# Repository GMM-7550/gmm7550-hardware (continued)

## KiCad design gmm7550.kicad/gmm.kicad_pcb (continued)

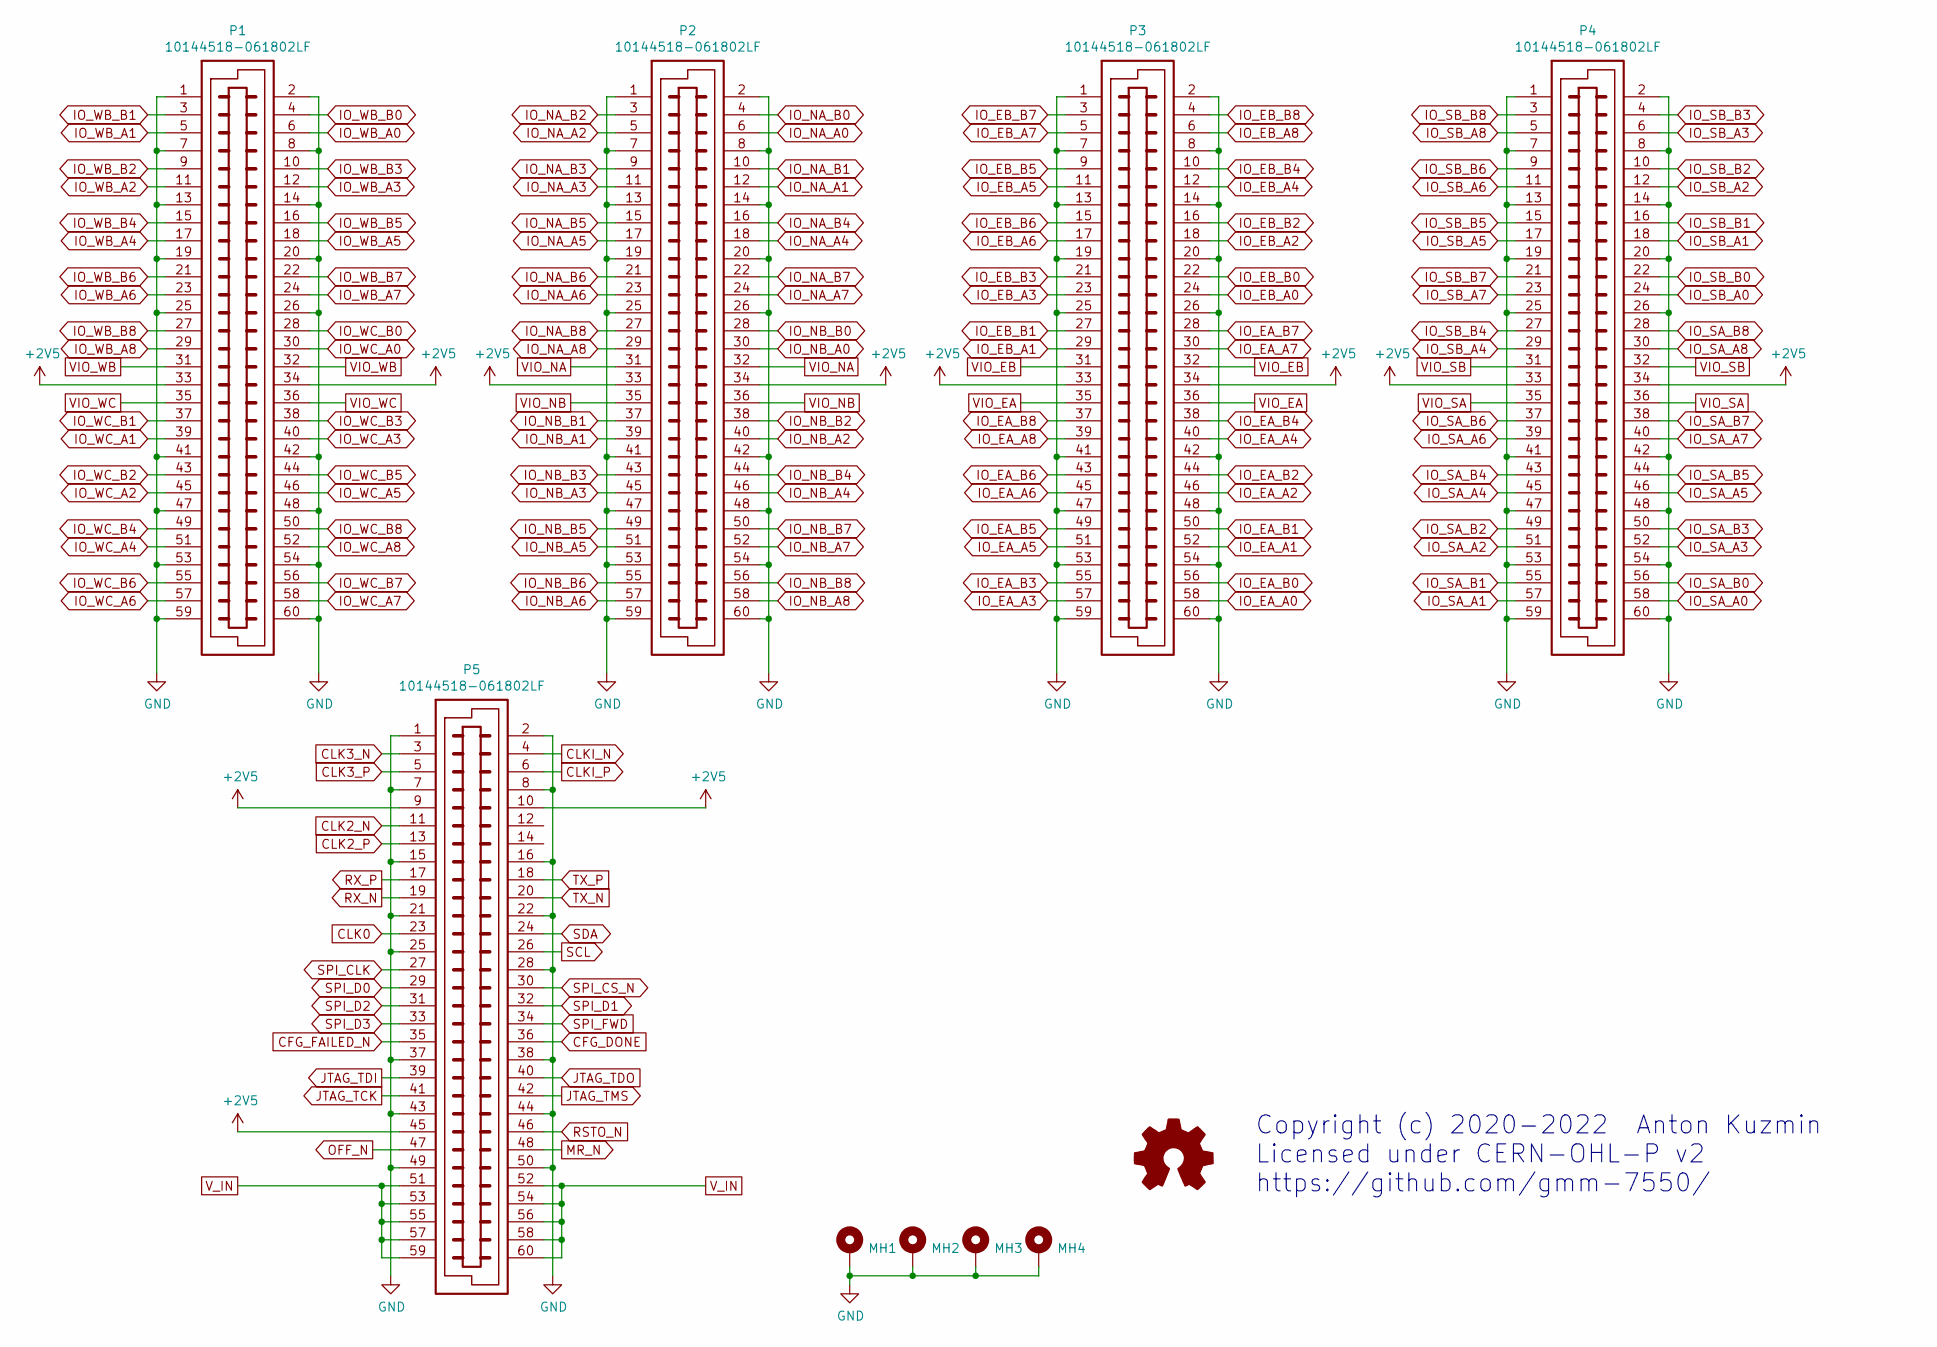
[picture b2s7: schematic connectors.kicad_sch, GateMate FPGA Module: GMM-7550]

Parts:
MH1, MH2, MH3, MH4: MountingHole_Pad; MountingHole_3.2mm_M3_ISO7380_Pad
P1, P2, P3, P4, P5: 10144518-061802LF

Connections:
+2V5: P1.33, P1.34, P2.33, P2.34, P3.33, P3.34, P4.33, P4.34, P5.9, P5.10, P5.45; also elsewhere on the board
CFG_DONE: P5.36; also elsewhere on the board
CFG_FAILED_N: P5.35; also elsewhere on the board
CLK0: P5.23; also elsewhere on the board
CLK2_N: P5.11; also elsewhere on the board
CLK2_P: P5.13; also elsewhere on the board
CLK3_N: P5.3; also elsewhere on the board
CLK3_P: P5.5; also elsewhere on the board
CLKI_N: P5.4; also elsewhere on the board
CLKI_P: P5.6; also elsewhere on the board
GND: MH1.1, MH2.1, MH3.1, MH4.1, P1.1, P1.2, P1.7, P1.8, P1.13, P1.14, P1.19, P1.20, P1.25, P1.26, P1.41, P1.42, P1.47, P1.48, P1.53, P1.54, P1.59, P1.60, P2.1, P2.2, P2.7, P2.8, P2.13, P2.14, P2.19, P2.20, P2.25, P2.26, P2.41, P2.42, P2.47, P2.48, P2.53, P2.54, P2.59, P2.60, P3.1, P3.2, P3.7, P3.8, P3.13, P3.14, P3.19, P3.20, P3.25, P3.26, P3.41, P3.42, P3.47, P3.48, P3.53, P3.54, P3.59, P3.60, P4.1, P4.2, P4.7, P4.8, P4.13, P4.14, P4.19, P4.20, P4.25, P4.26, P4.41, P4.42, P4.47, P4.48, P4.53, P4.54, P4.59, P4.60, P5.1, P5.2, P5.7, P5.8, P5.15, P5.16, P5.21, P5.22, P5.25, P5.28, P5.37, P5.38, P5.43, P5.44, P5.49, P5.50; also elsewhere on the board
IO_EA_A0: P3.58; also elsewhere on the board
IO_EA_A1: P3.52; also elsewhere on the board
IO_EA_A2: P3.46; also elsewhere on the board
IO_EA_A3: P3.57; also elsewhere on the board
IO_EA_A4: P3.40; also elsewhere on the board
IO_EA_A5: P3.51; also elsewhere on the board
IO_EA_A6: P3.45; also elsewhere on the board
IO_EA_A7: P3.30; also elsewhere on the board
IO_EA_A8: P3.39; also elsewhere on the board
IO_EA_B0: P3.56; also elsewhere on the board
IO_EA_B1: P3.50; also elsewhere on the board
IO_EA_B2: P3.44; also elsewhere on the board
IO_EA_B3: P3.55; also elsewhere on the board
IO_EA_B4: P3.38; also elsewhere on the board
IO_EA_B5: P3.49; also elsewhere on the board
IO_EA_B6: P3.43; also elsewhere on the board
IO_EA_B7: P3.28; also elsewhere on the board
IO_EA_B8: P3.37; also elsewhere on the board
IO_EB_A0: P3.24; also elsewhere on the board
IO_EB_A1: P3.29; also elsewhere on the board
IO_EB_A2: P3.18; also elsewhere on the board
IO_EB_A3: P3.23; also elsewhere on the board
IO_EB_A4: P3.12; also elsewhere on the board
IO_EB_A5: P3.11; also elsewhere on the board
IO_EB_A6: P3.17; also elsewhere on the board
IO_EB_A7: P3.5; also elsewhere on the board
IO_EB_A8: P3.6; also elsewhere on the board
IO_EB_B0: P3.22; also elsewhere on the board
IO_EB_B1: P3.27; also elsewhere on the board
IO_EB_B2: P3.16; also elsewhere on the board
IO_EB_B3: P3.21; also elsewhere on the board
IO_EB_B4: P3.10; also elsewhere on the board
IO_EB_B5: P3.9; also elsewhere on the board
IO_EB_B6: P3.15; also elsewhere on the board
IO_EB_B7: P3.3; also elsewhere on the board
IO_EB_B8: P3.4; also elsewhere on the board
IO_NA_A0: P2.6; also elsewhere on the board
IO_NA_A1: P2.12; also elsewhere on the board
IO_NA_A2: P2.5; also elsewhere on the board
IO_NA_A3: P2.11; also elsewhere on the board
IO_NA_A4: P2.18; also elsewhere on the board
IO_NA_A5: P2.17; also elsewhere on the board
IO_NA_A6: P2.23; also elsewhere on the board
IO_NA_A7: P2.24; also elsewhere on the board
IO_NA_A8: P2.29; also elsewhere on the board
IO_NA_B0: P2.4; also elsewhere on the board
IO_NA_B1: P2.10; also elsewhere on the board
IO_NA_B2: P2.3; also elsewhere on the board
IO_NA_B3: P2.9; also elsewhere on the board
IO_NA_B4: P2.16; also elsewhere on the board
IO_NA_B5: P2.15; also elsewhere on the board
IO_NA_B6: P2.21; also elsewhere on the board
IO_NA_B7: P2.22; also elsewhere on the board
IO_NA_B8: P2.27; also elsewhere on the board
IO_NB_A0: P2.30; also elsewhere on the board
IO_NB_A1: P2.39; also elsewhere on the board
IO_NB_A2: P2.40; also elsewhere on the board
IO_NB_A3: P2.45; also elsewhere on the board
IO_NB_A4: P2.46; also elsewhere on the board
IO_NB_A5: P2.51; also elsewhere on the board
IO_NB_A6: P2.57; also elsewhere on the board
IO_NB_A7: P2.52; also elsewhere on the board
IO_NB_A8: P2.58; also elsewhere on the board
IO_NB_B0: P2.28; also elsewhere on the board
IO_NB_B1: P2.37; also elsewhere on the board
IO_NB_B2: P2.38; also elsewhere on the board
IO_NB_B3: P2.43; also elsewhere on the board
IO_NB_B4: P2.44; also elsewhere on the board
IO_NB_B5: P2.49; also elsewhere on the board
IO_NB_B6: P2.55; also elsewhere on the board
IO_NB_B7: P2.50; also elsewhere on the board
IO_NB_B8: P2.56; also elsewhere on the board
IO_SA_A0: P4.58; also elsewhere on the board
IO_SA_A1: P4.57; also elsewhere on the board
IO_SA_A2: P4.51; also elsewhere on the board
IO_SA_A3: P4.52; also elsewhere on the board
IO_SA_A4: P4.45; also elsewhere on the board
IO_SA_A5: P4.46; also elsewhere on the board
IO_SA_A6: P4.39; also elsewhere on the board
IO_SA_A7: P4.40; also elsewhere on the board
IO_SA_A8: P4.30; also elsewhere on the board
IO_SA_B0: P4.56; also elsewhere on the board
IO_SA_B1: P4.55; also elsewhere on the board
IO_SA_B2: P4.49; also elsewhere on the board
IO_SA_B3: P4.50; also elsewhere on the board
IO_SA_B4: P4.43; also elsewhere on the board
IO_SA_B5: P4.44; also elsewhere on the board
IO_SA_B6: P4.37; also elsewhere on the board
IO_SA_B7: P4.38; also elsewhere on the board
IO_SA_B8: P4.28; also elsewhere on the board
IO_SB_A0: P4.24; also elsewhere on the board
IO_SB_A1: P4.18; also elsewhere on the board
IO_SB_A2: P4.12; also elsewhere on the board
IO_SB_A3: P4.6; also elsewhere on the board
IO_SB_A4: P4.29; also elsewhere on the board
IO_SB_A5: P4.17; also elsewhere on the board
IO_SB_A6: P4.11; also elsewhere on the board
IO_SB_A7: P4.23; also elsewhere on the board
IO_SB_A8: P4.5; also elsewhere on the board
IO_SB_B0: P4.22; also elsewhere on the board
IO_SB_B1: P4.16; also elsewhere on the board
IO_SB_B2: P4.10; also elsewhere on the board
IO_SB_B3: P4.4; also elsewhere on the board
IO_SB_B4: P4.27; also elsewhere on the board
IO_SB_B5: P4.15; also elsewhere on the board
IO_SB_B6: P4.9; also elsewhere on the board
IO_SB_B7: P4.21; also elsewhere on the board
IO_SB_B8: P4.3; also elsewhere on the board
IO_WB_A0: P1.6; also elsewhere on the board
IO_WB_A1: P1.5; also elsewhere on the board
IO_WB_A2: P1.11; also elsewhere on the board
IO_WB_A3: P1.12; also elsewhere on the board
IO_WB_A4: P1.17; also elsewhere on the board
IO_WB_A5: P1.18; also elsewhere on the board
IO_WB_A6: P1.23; also elsewhere on the board
IO_WB_A7: P1.24; also elsewhere on the board
IO_WB_A8: P1.29; also elsewhere on the board
IO_WB_B0: P1.4; also elsewhere on the board
IO_WB_B1: P1.3; also elsewhere on the board
IO_WB_B2: P1.9; also elsewhere on the board
IO_WB_B3: P1.10; also elsewhere on the board
IO_WB_B4: P1.15; also elsewhere on the board
IO_WB_B5: P1.16; also elsewhere on the board
IO_WB_B6: P1.21; also elsewhere on the board
IO_WB_B7: P1.22; also elsewhere on the board
IO_WB_B8: P1.27; also elsewhere on the board
IO_WC_A0: P1.30; also elsewhere on the board
IO_WC_A1: P1.39; also elsewhere on the board
IO_WC_A2: P1.45; also elsewhere on the board
IO_WC_A3: P1.40; also elsewhere on the board
IO_WC_A4: P1.51; also elsewhere on the board
IO_WC_A5: P1.46; also elsewhere on the board
IO_WC_A6: P1.57; also elsewhere on the board
IO_WC_A7: P1.58; also elsewhere on the board
IO_WC_A8: P1.52; also elsewhere on the board
IO_WC_B0: P1.28; also elsewhere on the board
IO_WC_B1: P1.37; also elsewhere on the board
IO_WC_B2: P1.43; also elsewhere on the board
IO_WC_B3: P1.38; also elsewhere on the board
IO_WC_B4: P1.49; also elsewhere on the board
IO_WC_B5: P1.44; also elsewhere on the board
IO_WC_B6: P1.55; also elsewhere on the board
IO_WC_B7: P1.56; also elsewhere on the board
IO_WC_B8: P1.50; also elsewhere on the board
JTAG_TCK: P5.41; also elsewhere on the board
JTAG_TDI: P5.39; also elsewhere on the board
JTAG_TDO: P5.40; also elsewhere on the board
JTAG_TMS: P5.42; also elsewhere on the board
MR_N: P5.48; also elsewhere on the board
OFF_N: P5.47; also elsewhere on the board
RSTO_N: P5.46; also elsewhere on the board
RX_N: P5.19; also elsewhere on the board
RX_P: P5.17; also elsewhere on the board
SCL: P5.26; also elsewhere on the board
SDA: P5.24; also elsewhere on the board
SPI_CLK: P5.27; also elsewhere on the board
SPI_CS_N: P5.30; also elsewhere on the board
SPI_D0: P5.29; also elsewhere on the board
SPI_D1: P5.32; also elsewhere on the board
SPI_D2: P5.31; also elsewhere on the board
SPI_D3: P5.33; also elsewhere on the board
SPI_FWD: P5.34; also elsewhere on the board
TX_N: P5.20; also elsewhere on the board
TX_P: P5.18; also elsewhere on the board
VIO_EA: P3.35, P3.36; also elsewhere on the board
VIO_EB: P3.31, P3.32; also elsewhere on the board
VIO_NA: P2.31, P2.32; also elsewhere on the board
VIO_NB: P2.35, P2.36; also elsewhere on the board
VIO_SA: P4.35, P4.36; also elsewhere on the board
VIO_SB: P4.31, P4.32; also elsewhere on the board
VIO_WB: P1.31, P1.32; also elsewhere on the board
VIO_WC: P1.35, P1.36; also elsewhere on the board
V_IN: P5.51, P5.52, P5.53, P5.54, P5.55, P5.56, P5.57, P5.58, P5.59, P5.60; also elsewhere on the board

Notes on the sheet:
Copyright (c) 2020-2022 Anton Kuzmin Licensed under CERN-OHL-P v2 https://github.com/gmm-7550/

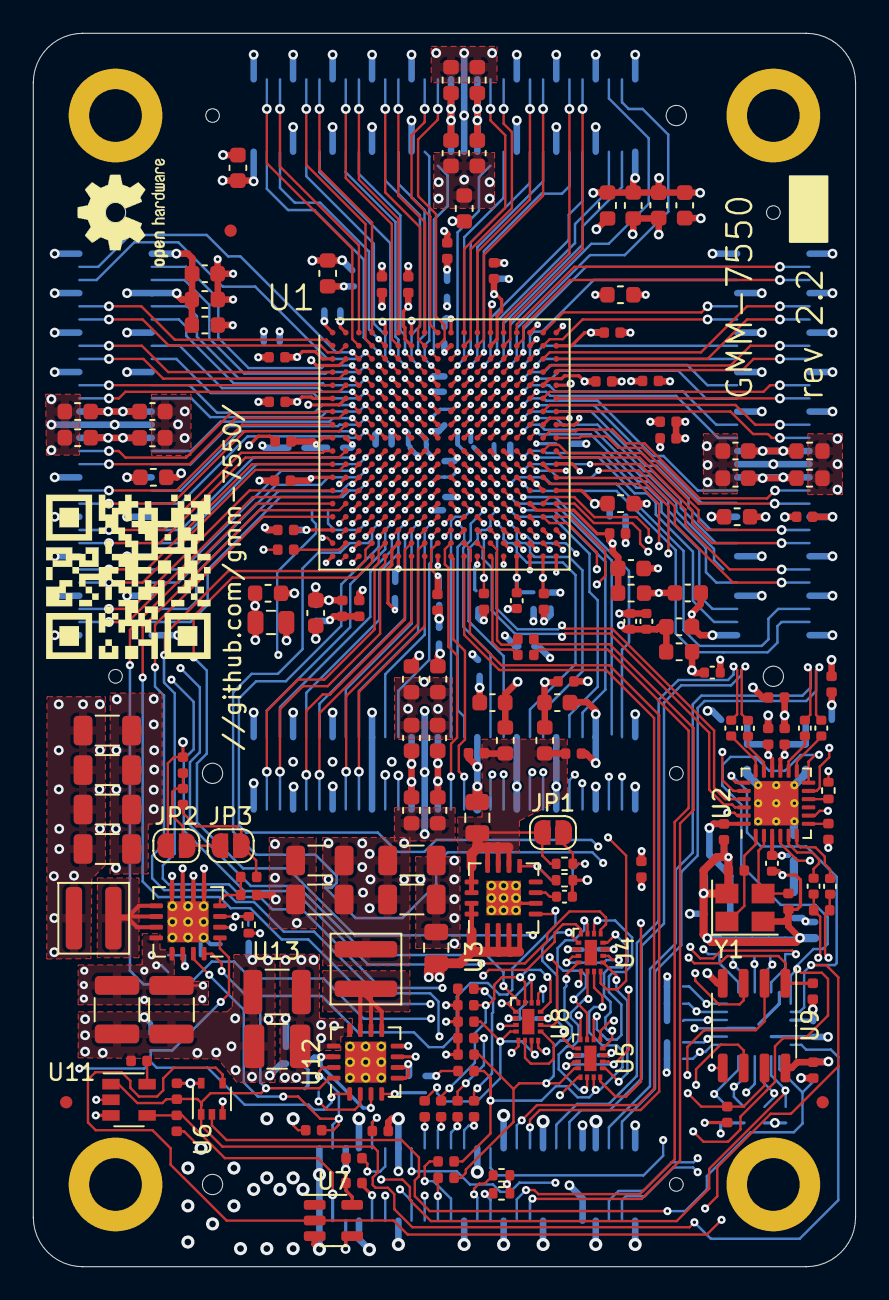
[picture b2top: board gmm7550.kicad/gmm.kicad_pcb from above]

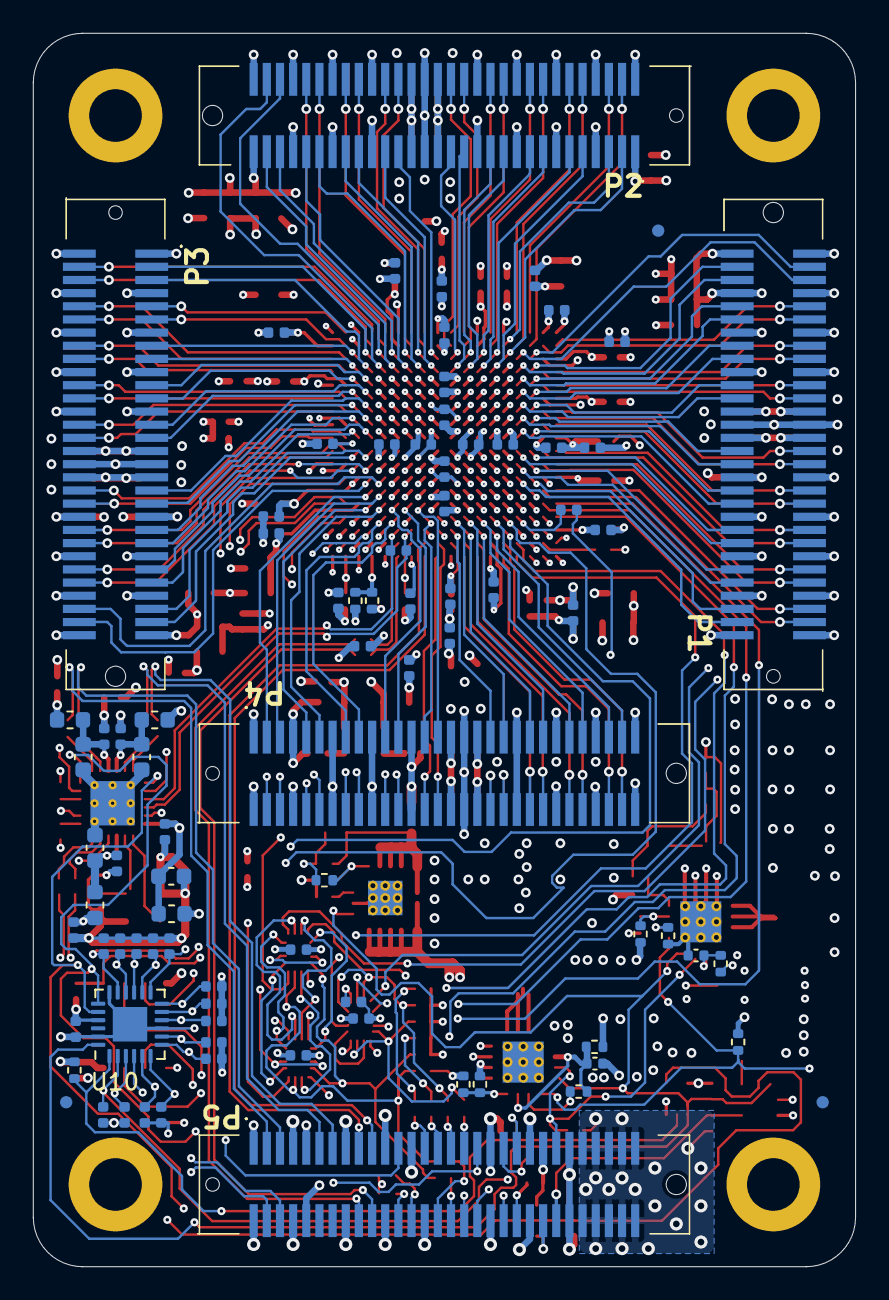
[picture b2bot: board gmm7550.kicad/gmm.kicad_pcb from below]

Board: 6 copper layers, 50.0 x 75.0 mm, 252 parts (86 on the bottom side), 268 nets.

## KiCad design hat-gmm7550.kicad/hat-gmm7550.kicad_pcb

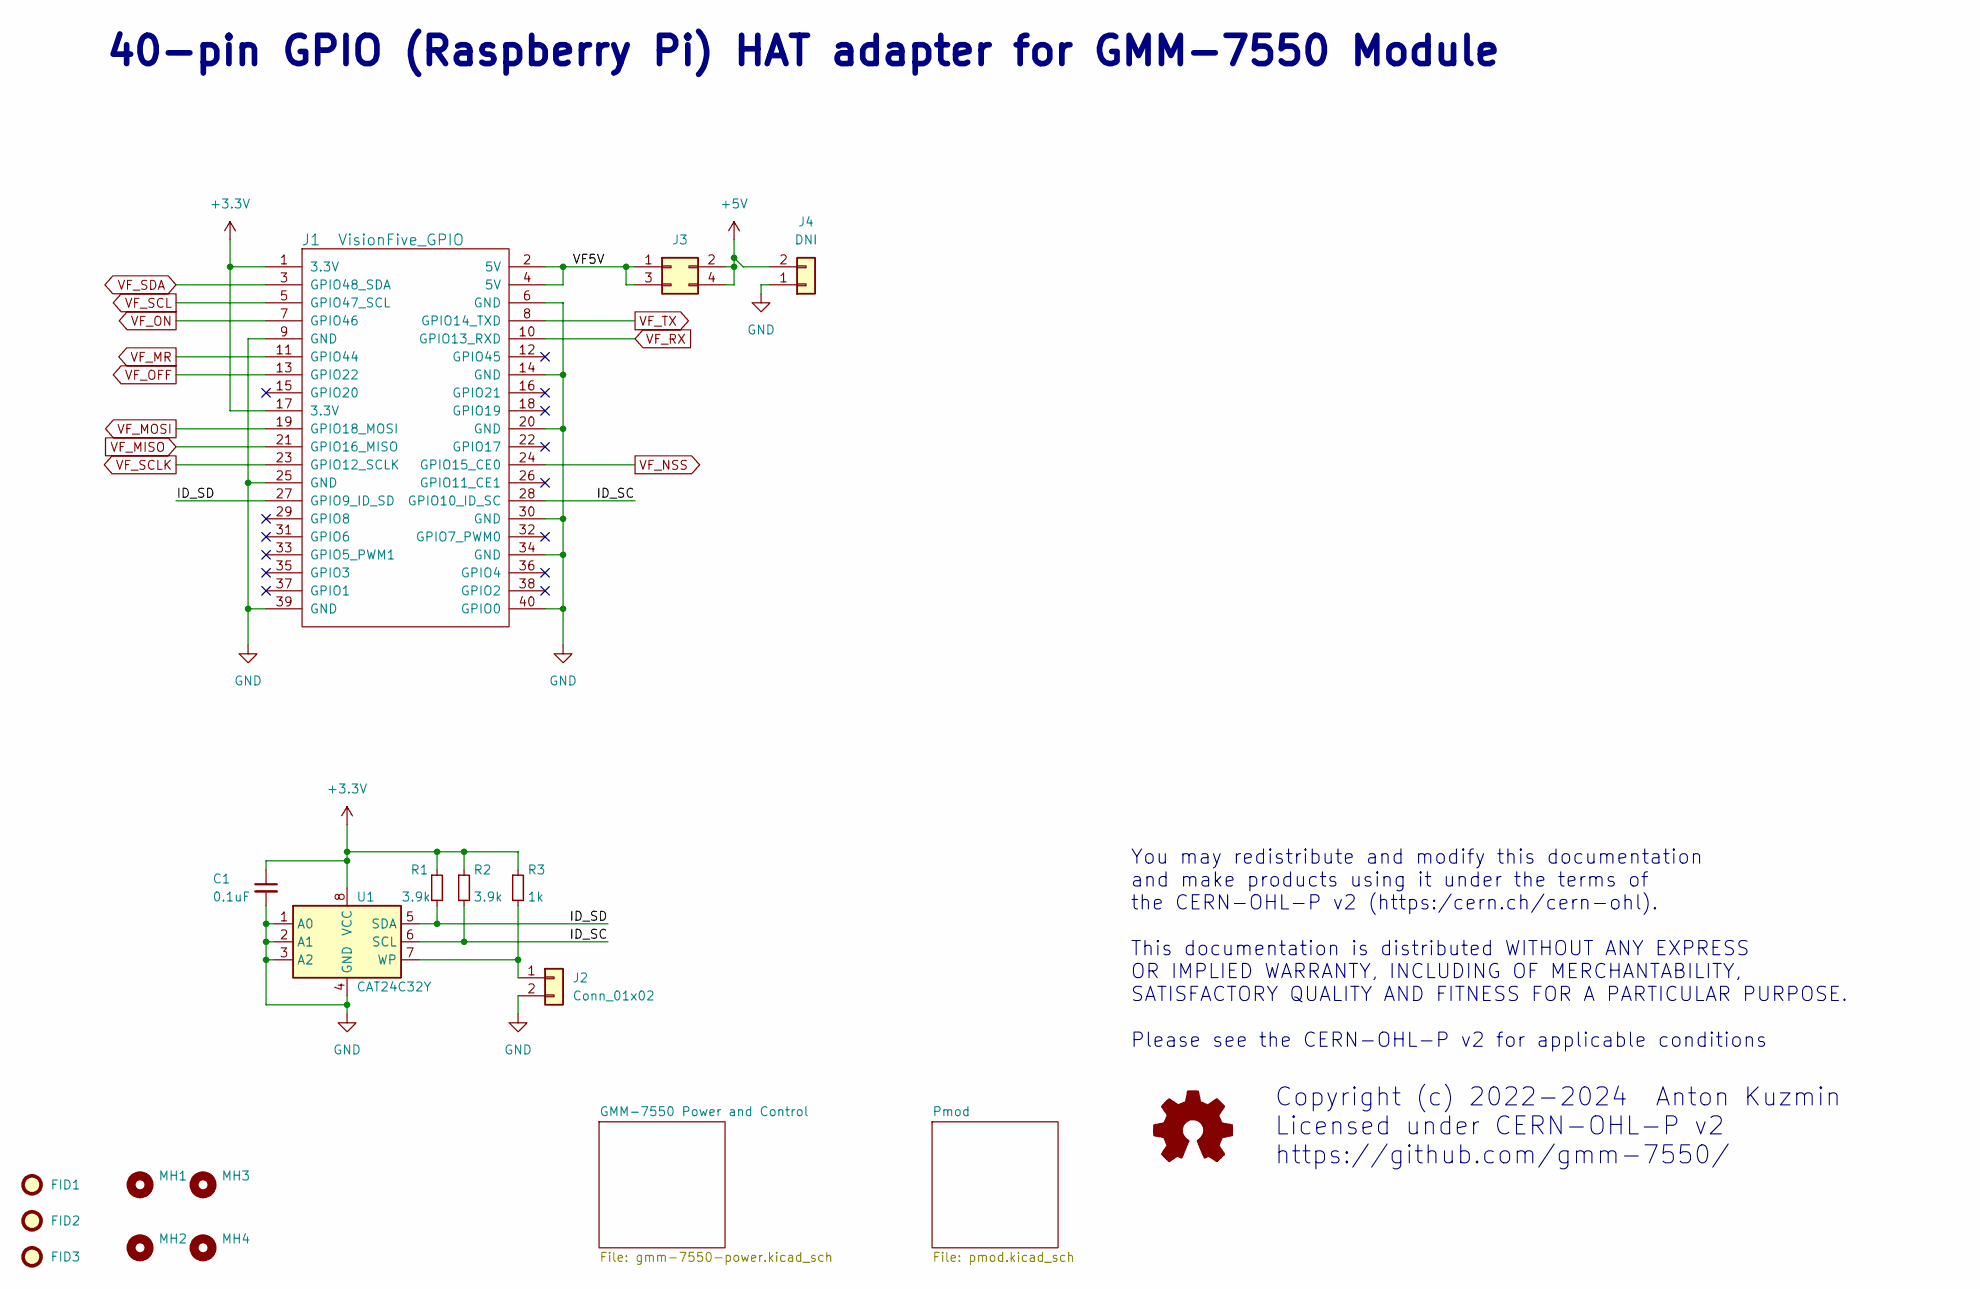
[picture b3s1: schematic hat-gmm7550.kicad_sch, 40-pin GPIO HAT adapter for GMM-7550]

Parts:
C1: 0.1uF; C_0603_1608Metric
FID1, FID2, FID3: Fiducial; Fiducial_1mm_Mask2mm
J1: VisionFive_GPIO; PinHeader_2x20_P2.54mm_Vertical
J2: Conn_01x02; PinHeader_1x02_P2.54mm_Vertical
J3: Conn_02x02_Odd_Even; PinHeader_2x02_P2.54mm_Vertical
J4: DNI; Molex_Micro-Fit_3.0_43045-0200_2x01_P3.00mm_Horizontal
MH1, MH2, MH3, MH4: MountingHole; RPi_Hat_Mounting_Hole
R1, R2: 3.9k; R_0603_1608Metric
R3: 1k; R_0603_1608Metric
U1: CAT24C32Y; TSSOP-8_4.4x3mm_P0.65mm

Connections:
+3V3: C1.1, J1.1 (3.3V), J1.17 (3.3V), R1.1, R2.1, R3.1, U1.8 (VCC); also elsewhere on the board
+5V: J3.2, J3.4, J4.2; also elsewhere on the board
/ID_SC: J1.28 (GPIO10_ID_SC), R2.2, U1.6 (SCL)
/ID_SD: J1.27 (GPIO9_ID_SD), R1.2, U1.5 (SDA)
/VF5V: J1.2 (5V), J1.4 (5V), J3.1, J3.3
GND: C1.2, J1.6 (GND), J1.9 (GND), J1.14 (GND), J1.20 (GND), J1.25 (GND), J1.30 (GND), J1.34 (GND), J1.39 (GND), J1.40 (GPIO0), J2.2, J4.1, U1.1 (A0), U1.2 (A1), U1.3 (A2), U1.4 (GND); also elsewhere on the board
unnamed: J2.1, R3.2, U1.7 (WP)
VF_MISO: J1.21 (GPIO16_MISO); also elsewhere on the board
VF_MOSI: J1.19 (GPIO18_MOSI); also elsewhere on the board
VF_MR: J1.11 (GPIO44); also elsewhere on the board
VF_NSS: J1.24 (GPIO15_CE0); also elsewhere on the board
VF_OFF: J1.13 (GPIO22); also elsewhere on the board
VF_ON: J1.7 (GPIO46); also elsewhere on the board
VF_RX: J1.10 (GPIO13_RXD); also elsewhere on the board
VF_SCL: J1.5 (GPIO47_SCL); also elsewhere on the board
VF_SCLK: J1.23 (GPIO12_SCLK); also elsewhere on the board
VF_SDA: J1.3 (GPIO48_SDA); also elsewhere on the board
VF_TX: J1.8 (GPIO14_TXD); also elsewhere on the board

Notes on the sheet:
Copyright (c) 2022-2024 Anton Kuzmin Licensed under CERN-OHL-P v2 https://github.com/gmm-7550/
40-pin GPIO (Raspberry Pi) HAT adapter for GMM-7550 Module
You may redistribute and modify this documentation and make products using it under the terms of the CERN-OHL-P v2 (https:/cern.ch/cern-ohl). This documentation is distributed WITHOUT ANY EXPRESS OR IMPLIED WARRANTY, INCLUDING OF MERCHANTABILITY, SATISFACTORY QUALITY AND FITNESS FOR A PARTICULAR PU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

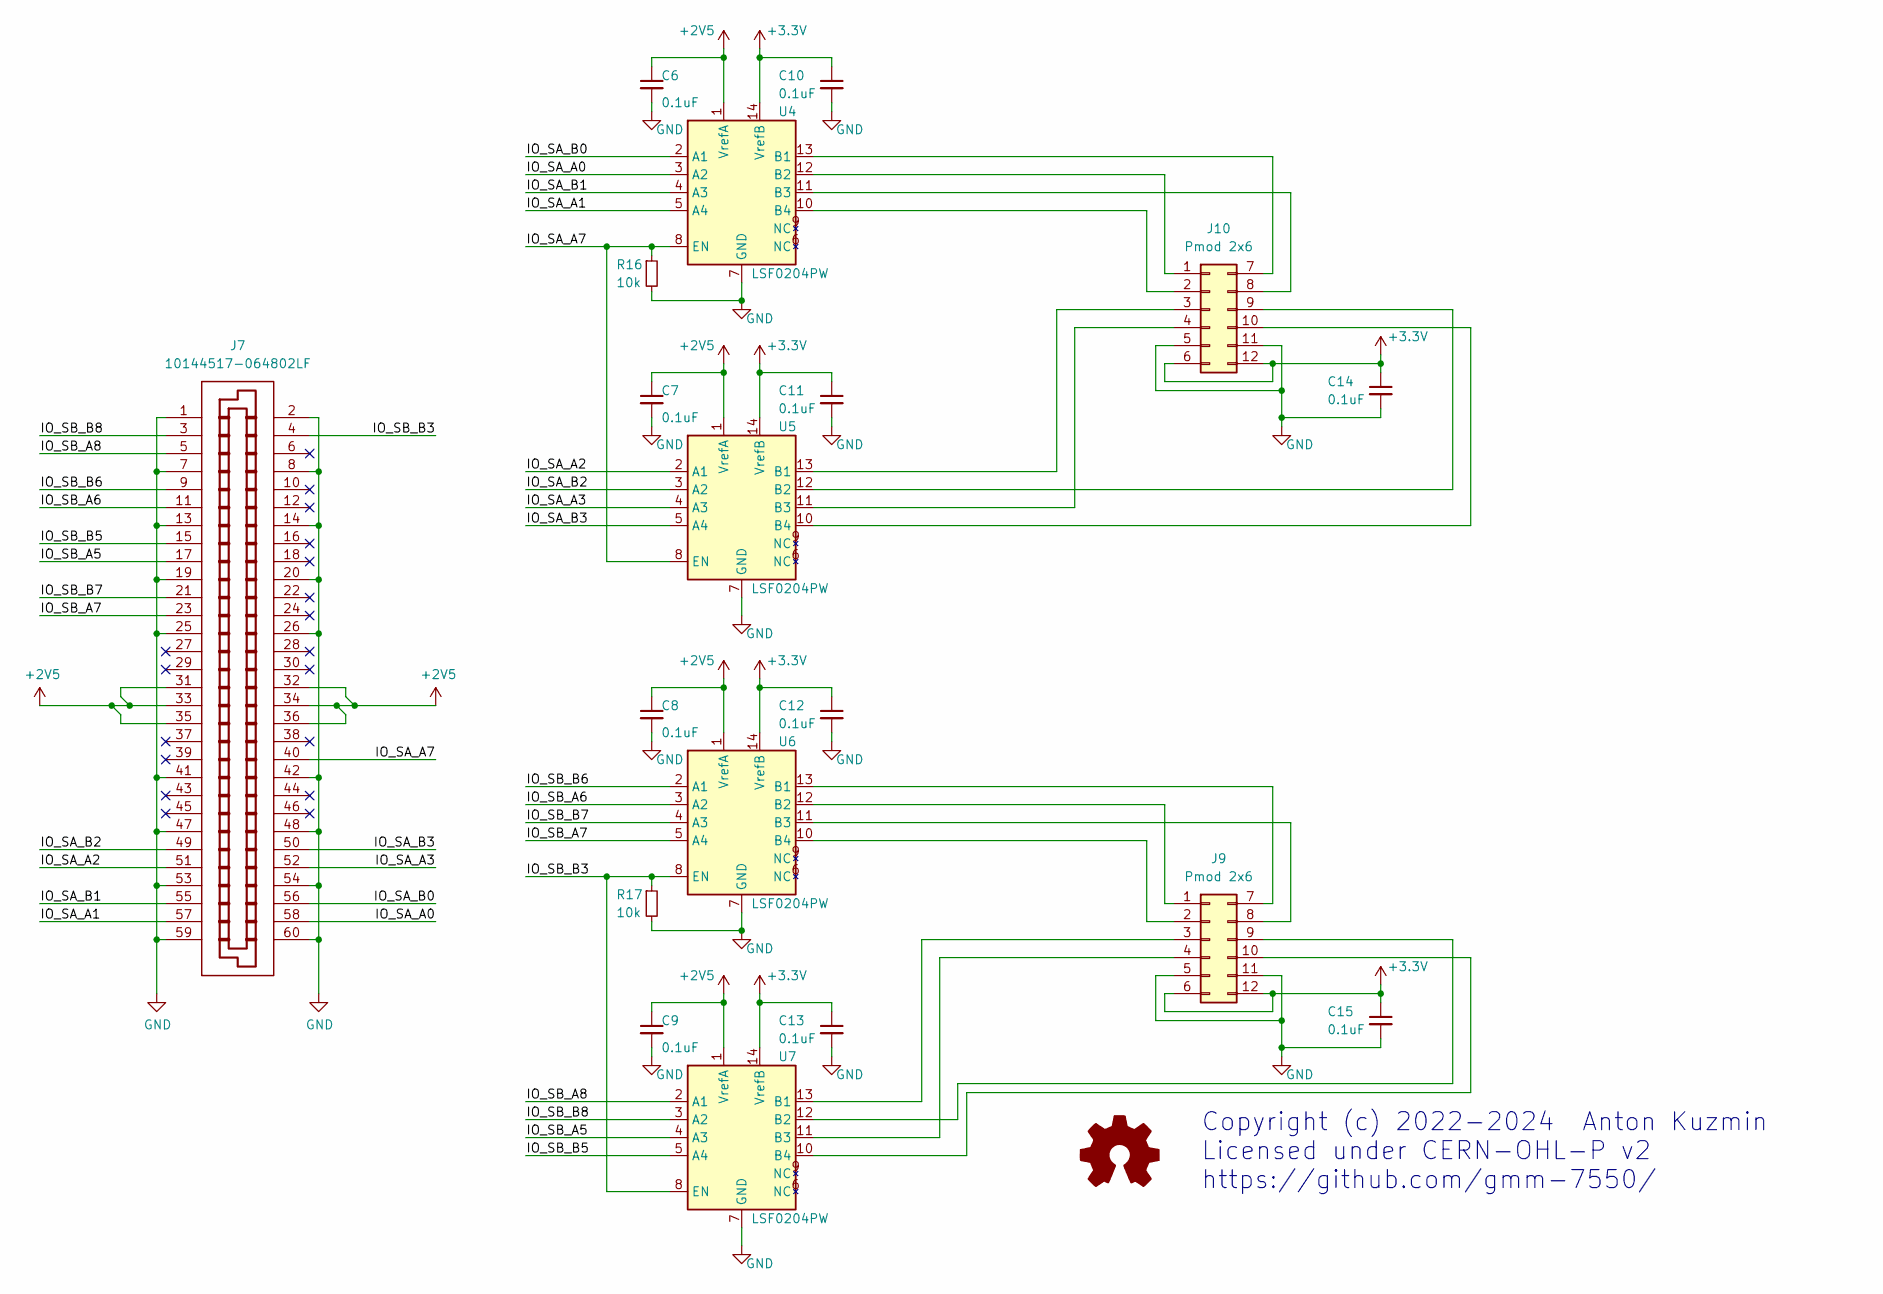
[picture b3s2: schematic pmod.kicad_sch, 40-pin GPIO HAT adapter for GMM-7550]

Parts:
C6, C7, C8, C9, C10, C11, C12, C13, C14, C15: 0.1uF; C_0603_1608Metric
J7: 10144517-064802LF; 10144517-061802LF
J9, J10: Pmod 2x6; PmodSocket_2x06_P2.54mm_Horizontal
R16, R17: 10k; R_0603_1608Metric
U4, U5, U6, U7: LSF0204PW; TSSOP-14_4.4x5mm_P0.65mm

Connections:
+2V5: C6.1, C7.1, C8.1, C9.1, J7.31, J7.32, J7.33, J7.34, J7.35, J7.36, U4.1 (VrefA), U5.1 (VrefA), U6.1 (VrefA), U7.1 (VrefA); also elsewhere on the board
+3V3: C10.1, C11.1, C12.1, C13.1, C14.1, C15.1, J9.6, J9.12, J10.6, J10.12, U4.14 (VrefB), U5.14 (VrefB), U6.14 (VrefB), U7.14 (VrefB); also elsewhere on the board
/Pmod/IO_SA_A0: J7.58, U4.3 (A2)
/Pmod/IO_SA_A1: J7.57, U4.5 (A4)
/Pmod/IO_SA_A2: J7.51, U5.2 (A1)
/Pmod/IO_SA_A3: J7.52, U5.4 (A3)
/Pmod/IO_SA_A7: J7.40, R16.1, U4.8 (EN), U5.8 (EN)
/Pmod/IO_SA_B0: J7.56, U4.2 (A1)
/Pmod/IO_SA_B1: J7.55, U4.4 (A3)
/Pmod/IO_SA_B2: J7.49, U5.3 (A2)
/Pmod/IO_SA_B3: J7.50, U5.5 (A4)
/Pmod/IO_SB_A5: J7.17, U7.4 (A3)
/Pmod/IO_SB_A6: J7.11, U6.3 (A2)
/Pmod/IO_SB_A7: J7.23, U6.5 (A4)
/Pmod/IO_SB_A8: J7.5, U7.2 (A1)
/Pmod/IO_SB_B3: J7.4, R17.1, U6.8 (EN), U7.8 (EN)
/Pmod/IO_SB_B5: J7.15, U7.5 (A4)
/Pmod/IO_SB_B6: J7.9, U6.2 (A1)
/Pmod/IO_SB_B7: J7.21, U6.4 (A3)
/Pmod/IO_SB_B8: J7.3, U7.3 (A2)
GND: C6.2, C7.2, C8.2, C9.2, C10.2, C11.2, C12.2, C13.2, C14.2, C15.2, J7.1, J7.2, J7.7, J7.8, J7.13, J7.14, J7.19, J7.20, J7.25, J7.26, J7.41, J7.42, J7.47, J7.48, J7.53, J7.54, J7.59, J7.60, J9.5, J9.11, J10.5, J10.11, R16.2, R17.2, U4.7 (GND), U5.7 (GND), U6.7 (GND), U7.7 (GND); also elsewhere on the board
unnamed: J9.1, U6.12 (B2)
unnamed: J9.2, U6.10 (B4)
unnamed: J9.3, U7.13 (B1)
unnamed: J9.4, U7.11 (B3)
unnamed: J9.7, U6.13 (B1)
unnamed: J9.8, U6.11 (B3)
unnamed: J9.9, U7.12 (B2)
unnamed: J9.10, U7.10 (B4)
unnamed: J10.1, U4.12 (B2)
unnamed: J10.2, U4.10 (B4)
unnamed: J10.3, U5.13 (B1)
unnamed: J10.4, U5.11 (B3)
unnamed: J10.7, U4.13 (B1)
unnamed: J10.8, U4.11 (B3)
unnamed: J10.9, U5.12 (B2)
unnamed: J10.10, U5.10 (B4)

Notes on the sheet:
Copyright (c) 2022-2024 Anton Kuzmin Licensed under CERN-OHL-P v2 https://github.com/gmm-7550/
